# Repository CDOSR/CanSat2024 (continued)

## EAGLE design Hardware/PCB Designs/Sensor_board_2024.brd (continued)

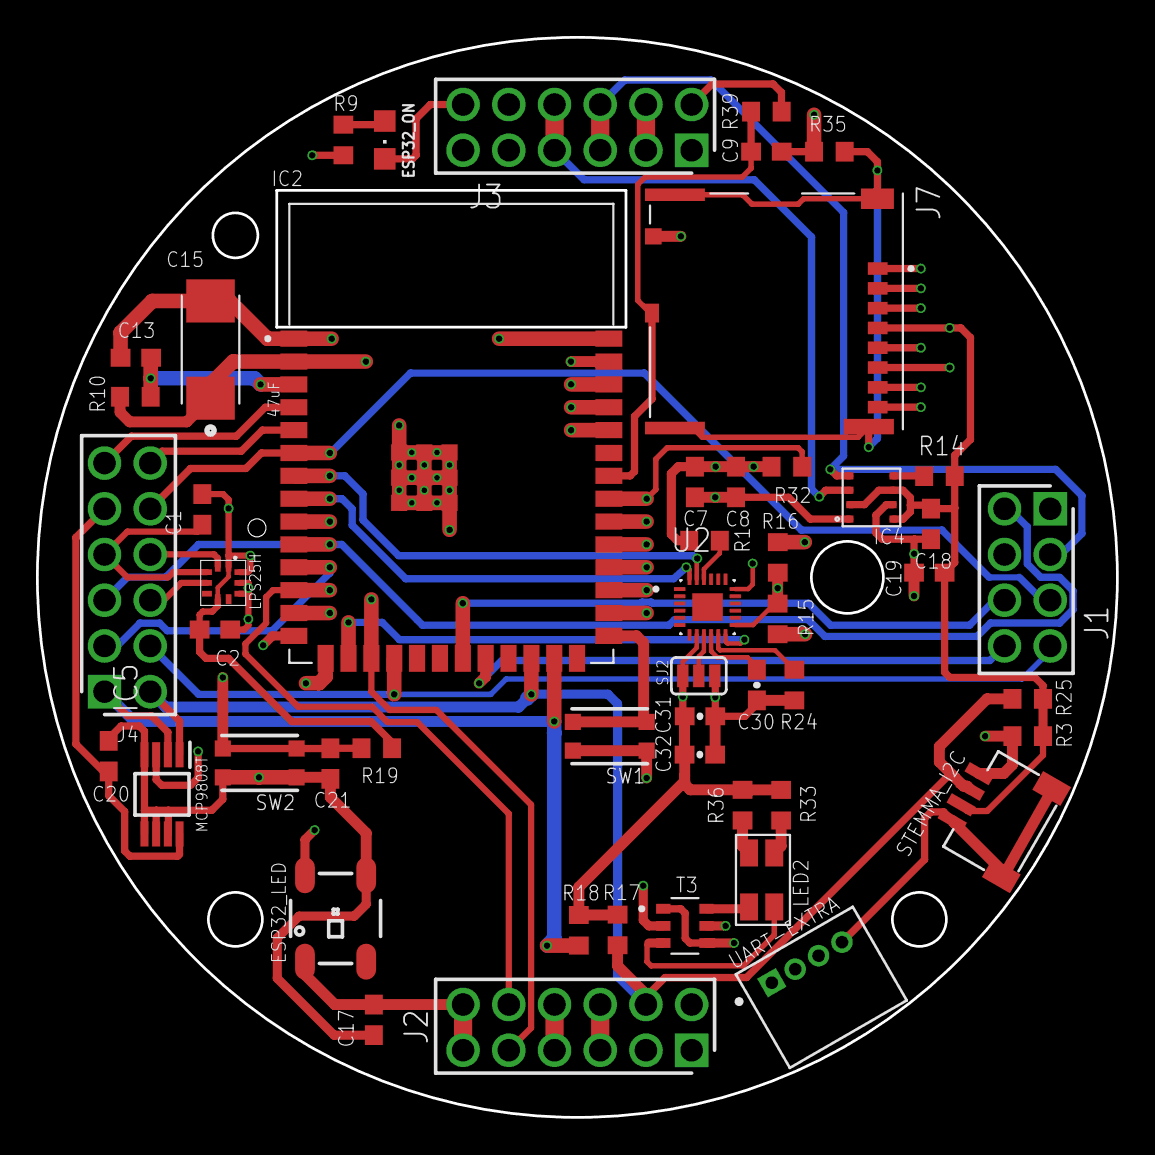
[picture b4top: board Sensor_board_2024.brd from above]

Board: 4 copper layers, 60.0 x 60.0 mm, 51 parts (0 on the bottom side), 45 nets.

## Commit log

2024-05-27 Version 0.1 for the Lora based Base Station
2024-05-29 Main Can software version 0.1
2024-05-30 Clean up
2024-05-30 Documentation update
2024-06-01 Updated to a newer version
2024-06-01 Added requirements.txt
2024-06-01 Added Temperature, Pressure and Altitude combo grapher
2024-06-01 Renamed requirements.txt
2024-06-01 Updated requirements.txt
2024-06-01 Updated JSON Converter and Validator, and Graph Plotters
2024-06-02 Update to Grapher program Log file added
2026-04-15 chore: ignore pybytes_config.json
2026-04-15 Add 2024 PDR and CDR LaTeX sources under Mission Docs
    Imported from the CDOSR---2024-PDR Overleaf repo, split into:
    - PDR/src/: RCRC_PDR_CDOSR.tex + section_1..7
    - CDR/src/: CanSat_CDR_CDOSR.tex
    - common/: shared style images and icons
    Dropped ROSPIN guideline templates (CDR.tex, CanSat_PDR_Empty.tex,
    PDR_Evaluation.tex), unused assets (hyperendnotes.sty, the 5.6 MB
2026-04-15 chore: ignore LaTeX build artifacts
2026-04-15 fix: restore hyperendnotes.sty required by CDOSR_CanSat.sty
    CDOSR_CanSat.sty:23 \RequirePackage{hyperendnotes} — missed on the
    first pass because the usage is in a .sty, not a .tex file.
2026-04-15 Consolidate loose images under common/images/
    - Move img_CDOSR.png, img_CANSAT_RO.png, img_Block_Diagram_2023.eps
    from common/ root into common/images/
    - Restore img_Cansats_in_europe.png (referenced from
    CDOSR_CanSat.sty:86 fancy footer — I missed it on first pass
    because my reference scan only covered .tex, not .sty)
    - Update the 7 references in both CDOSR_CanSat.sty copies and both
2026-04-15 Pre-convert EPS to PDF to avoid MiKTeX restricted-mode failure
    MiKTeX's bundled epstopdf runs in restricted mode and refuses input
    paths containing '..' — the cross-directory hop to common/images/
    tripped it with 'Input file name not allowed in restricted mode'.
    Fix: convert all 4 .eps files to .pdf using TinyTeX's epstopdf
    (Ghostscript under the hood) and drop the .eps extension from
    the 5 active \includegraphics calls so pdflatex auto-picks the .pdf.
2026-04-15 fix(pdr): drop orphan \end{enumerate} in subsection_7_2
    The Recommendations paragraph had a stray \end{enumerate} closing
    an environment that was never opened — a leftover from refactoring
    a list into prose. enumitem raised 'Undefined control sequence
    \enit@after' because \enit@endenumerate was called without a
    matching \begin{enumerate}.
    Pre-existing bug inherited from the Overleaf import.
2026-04-15 fix(latex): repair legacy Overleaf source bugs
    Three pre-existing issues from the Overleaf import, all inherited:
    1. CDR CanSat_CDR_CDOSR.tex:84 — \caption and \label were outside
    the \end{table}, triggering "\caption outside float". Moved
    them inside the table float.
    2. PDR RCRC_PDR_CDOSR.tex — duplicate \end{document} (original at
    line 365, orphan at 367). LaTeX silently ignores the second one
2026-04-15 Replace CDR source with canonical RCRC---2024-CDR-good-bkp- import
    The previous CDR/src/ came from the CDOSR---2024-PDR repo and was
    a 2023-vintage standalone draft riddled with legacy bugs. Replaced
    with the canonical CDR source from derzse/RCRC---2024-CDR-good-bkp-
    (dated May 10, 2024), which uses a section-ized structure matching
    the PDR.
    - Delete: CDR/src/CanSat_CDR_CDOSR.tex (old 2023 standalone)
2026-04-15 rename(cdr): can_2024 render to sane filename
    The new CDR referenced a 108-char PNG named from an Overleaf upload:
    can_2024_2024-May-15_03-51-36PM-000_CustomizedView11299654543_png_-_Copy-removebg-preview.png
    Renamed to can_2024_render.png. Same bytes, updated the two
    references in section_2/subsection_2_{1,2}.tex.
2026-04-15 rename: main tex files to CanSat_2024_{PDR,CDR}_CDOSR.tex
    Match the existing compiled-PDF naming convention under
    Documentation/Mission Docs/{PDR,CDR}/ and drop the RCRC prefix.
    - PDR/src/RCRC_PDR_CDOSR.tex -> CanSat_2024_PDR_CDOSR.tex
    - CDR/src/RCRC_CDR_CDOSR.tex -> CanSat_2024_CDR_CDOSR.tex
    No other files reference these by name, so no source edits needed.
2026-04-15 rename: CanSat_2024_CDR__CDOSR_.pdf -> CanSat_2024_CDR_CDOSR.pdf
    Drop the stray double-underscore and trailing underscore in the
    compiled CDR filename to match the PDR's CanSat_2024_PDR_CDOSR.pdf
    convention and the source name in CDR/src/.
2026-04-15 docs: rewrite Mission Docs README with PDR/CDR build instructions
    Rename readme.md -> README.md (case convention) and populate the
    previously-empty stub with:
    - Directory layout under Mission Docs/
    - pdflatex build commands for both documents
    - Notes on the EPS->PDF pre-conversion workaround, shared .sty
    duplication, and team roster inclusion
2026-04-15 docs: clarify split between Hardware/ and Documentation/Hardware/
    The team's CAD sources (Eagle .sch/.brd) live at the repo root under
    Hardware/PCB Designs/, while third-party component datasheets live
    under Documentation/Hardware/Data Sheets/. Keep them where they are
    and cross-reference so anyone browsing either tree knows the other
    half exists.
    - Hardware/readme.md: drop references to the nonexistent Schematics/
2026-04-15 Add EAGLE PCB sources for 4 custom 2024 boards
    Schematic and board layout files for the four boards designed for
    CanSat 2024:
    - Comm_board_2024_L76 (Quectel L76 GNSS)
    - Comm_board_2024_M8N (u-blox NEO-M8N GNSS)
    - Power_board_2024
    - Sensor_board_2024
2026-04-15 ci: add Dependabot config for pip and github-actions
    Weekly updates for:
    - pip: Software/Data Analysis/requirements.txt
    (folium, pandas, matplotlib, seaborn)
    - github-actions: registered preemptively so any future workflow
    under .github/workflows/ is automatically monitored
    Runs Monday 07:00 Europe/Bucharest. PRs land with chore(deps)
